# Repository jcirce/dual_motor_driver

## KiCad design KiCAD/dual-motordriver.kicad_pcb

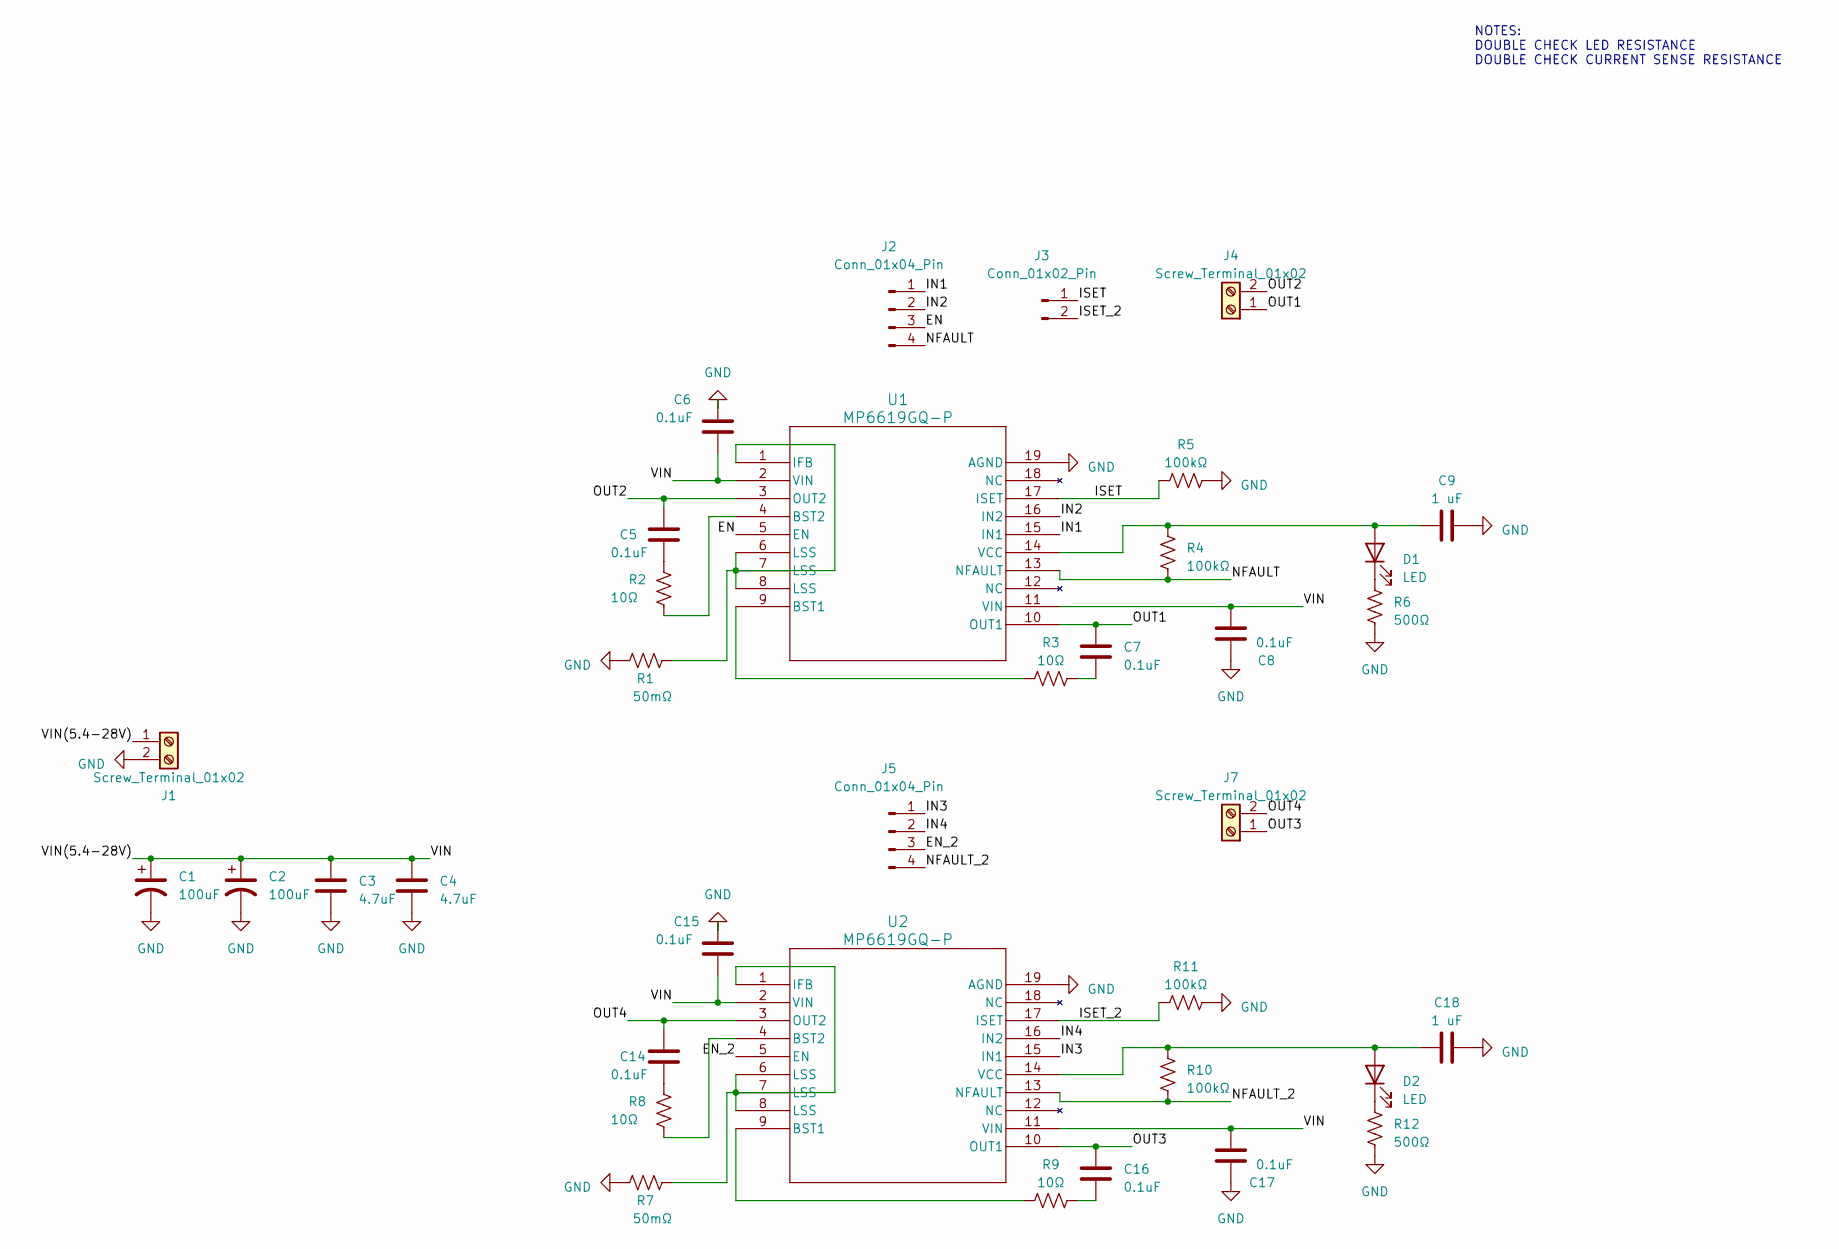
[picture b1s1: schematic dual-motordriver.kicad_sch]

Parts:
C1, C2: 100uF; CP_Elec_8x11.9
C3, C4: 4.7uF; C_0805_2012Metric
C5, C6, C7, C8, C14, C15, C16, C17: 0.1uF; C_0603_1608Metric
C9, C18: 1 uF; C_0805_2012Metric
D1, D2: LED; D_0603_1608Metric
J1, J4, J7: Screw_Terminal_01x02; TCxx03_5mm_2x1
J2, J5: Conn_01x04_Pin; PinHeader_1x04_P2.54mm_Vertical
J3: Conn_01x02_Pin; PinHeader_1x02_P2.54mm_Vertical
R1, R7: 50mΩ; R_0603_1608Metric
R2, R3, R8, R9: 10Ω; R_0603_1608Metric
R4, R5, R10, R11: 100kΩ; R_0603_1608Metric
R6, R12: 500Ω; R_0603_1608Metric
U1, U2: MP6619GQ-P; QFN-19_MP6619

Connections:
/EN: J2.3, U1.5 (EN)
/EN_2: J5.3, U2.5 (EN)
/IN1: J2.1, U1.15 (IN1)
/IN2: J2.2, U1.16 (IN2)
/IN3: J5.1, U2.15 (IN1)
/IN4: J5.2, U2.16 (IN2)
/ISET: J3.1, R5.1, U1.17 (ISET)
/ISET_2: J3.2, R11.1, U2.17 (ISET)
/NFAULT: J2.4, R4.2, U1.13 (NFAULT)
/NFAULT_2: J5.4, R10.2, U2.13 (NFAULT)
/OUT1: C7.1, J4.1, U1.10 (OUT1)
/OUT2: C5.2, J4.2, U1.3 (OUT2)
/OUT3: C16.1, J7.1, U2.10 (OUT1)
/OUT4: C14.2, J7.2, U2.3 (OUT2)
/VIN: C1.1, C2.1, C3.1, C4.1, C6.1, C8.1, C15.1, C17.1, J1.1, U1.2 (VIN), U1.11 (VIN), U2.2 (VIN), U2.11 (VIN)
GND: C1.2, C2.2, C3.2, C4.2, C6.2, C8.2, C9.2, C15.2, C17.2, C18.2, J1.2, R1.2, R5.2, R6.2, R7.2, R11.2, R12.2, U1.19 (AGND), U2.19 (AGND)
unnamed: C5.1, R2.2
unnamed: C7.2, R3.2
unnamed: C14.1, R8.2
unnamed: C16.2, R9.2
unnamed: C9.1, D1.2 (A), R4.1, U1.14 (VCC)
unnamed: D1.1 (K), R6.1
unnamed: C18.1, D2.2 (A), R10.1, U2.14 (VCC)
unnamed: D2.1 (K), R12.1
unnamed: R3.1, U1.9 (BST1)
unnamed: R2.1, U1.4 (BST2)
unnamed: R1.1, U1.1 (IFB), U1.6 (LSS), U1.7 (LSS), U1.8 (LSS)
unnamed: R9.1, U2.9 (BST1)
unnamed: R8.1, U2.4 (BST2)
unnamed: R7.1, U2.1 (IFB), U2.6 (LSS), U2.7 (LSS), U2.8 (LSS)

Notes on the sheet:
NOTES: DOUBLE CHECK LED RESISTANCE DOUBLE CHECK CURRENT SENSE RESISTANCE

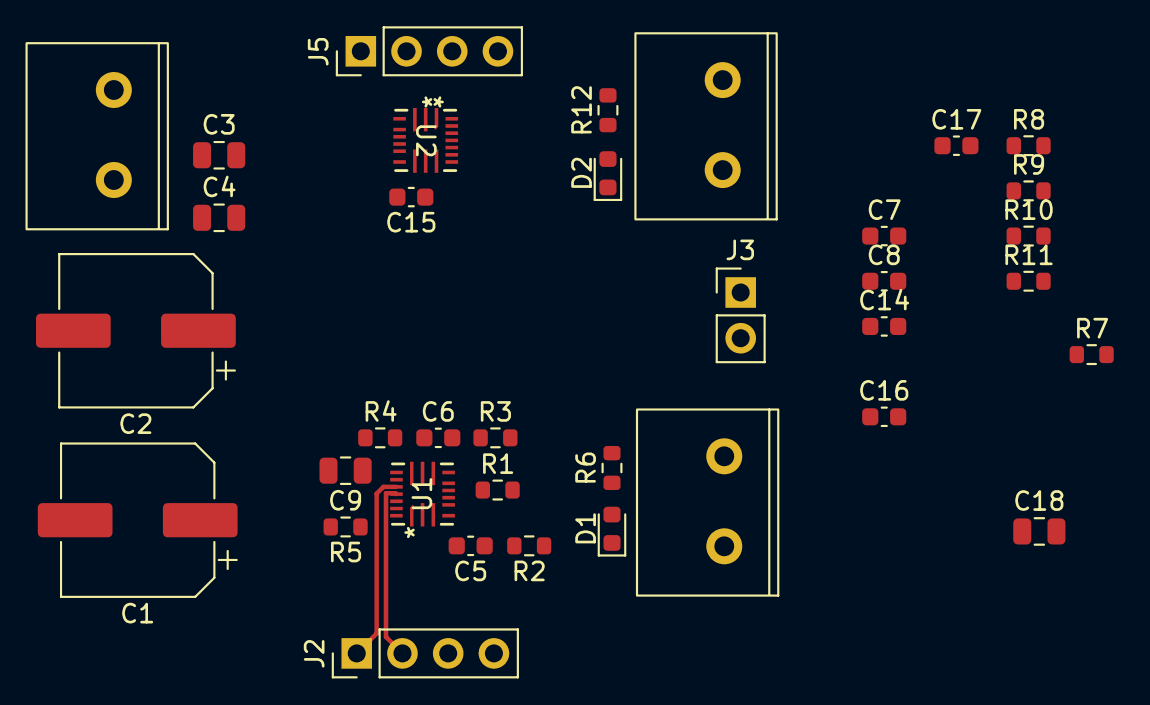
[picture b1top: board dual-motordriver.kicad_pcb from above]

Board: 2 copper layers, 36 parts (0 on the bottom side), 30 nets.

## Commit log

2023-04-19 schematic mostly outlined, assigned footprints
